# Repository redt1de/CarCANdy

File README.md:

# CarCANdy

# TODO:
- (V2) re-wire the RJ45 connector so pairs or together and in order
- add "live" capture to cli that will read from serial

# SN65HVD233DR Mode select pin (Rs): 
    high speed mode:    JP 2->1 and solder RS
    slope control mode: JP 2->1 and open RS
    low power mode:     JP 2->3

# Aux Ports
    include/AuxPorts.h
    AUX1: digital, UART,PWM
        28: RX,D28
        29: TX,D28

    AUX2: digital,analog,UART,PWM
        24: TX,D24,A10
        25: RX,D25,A11

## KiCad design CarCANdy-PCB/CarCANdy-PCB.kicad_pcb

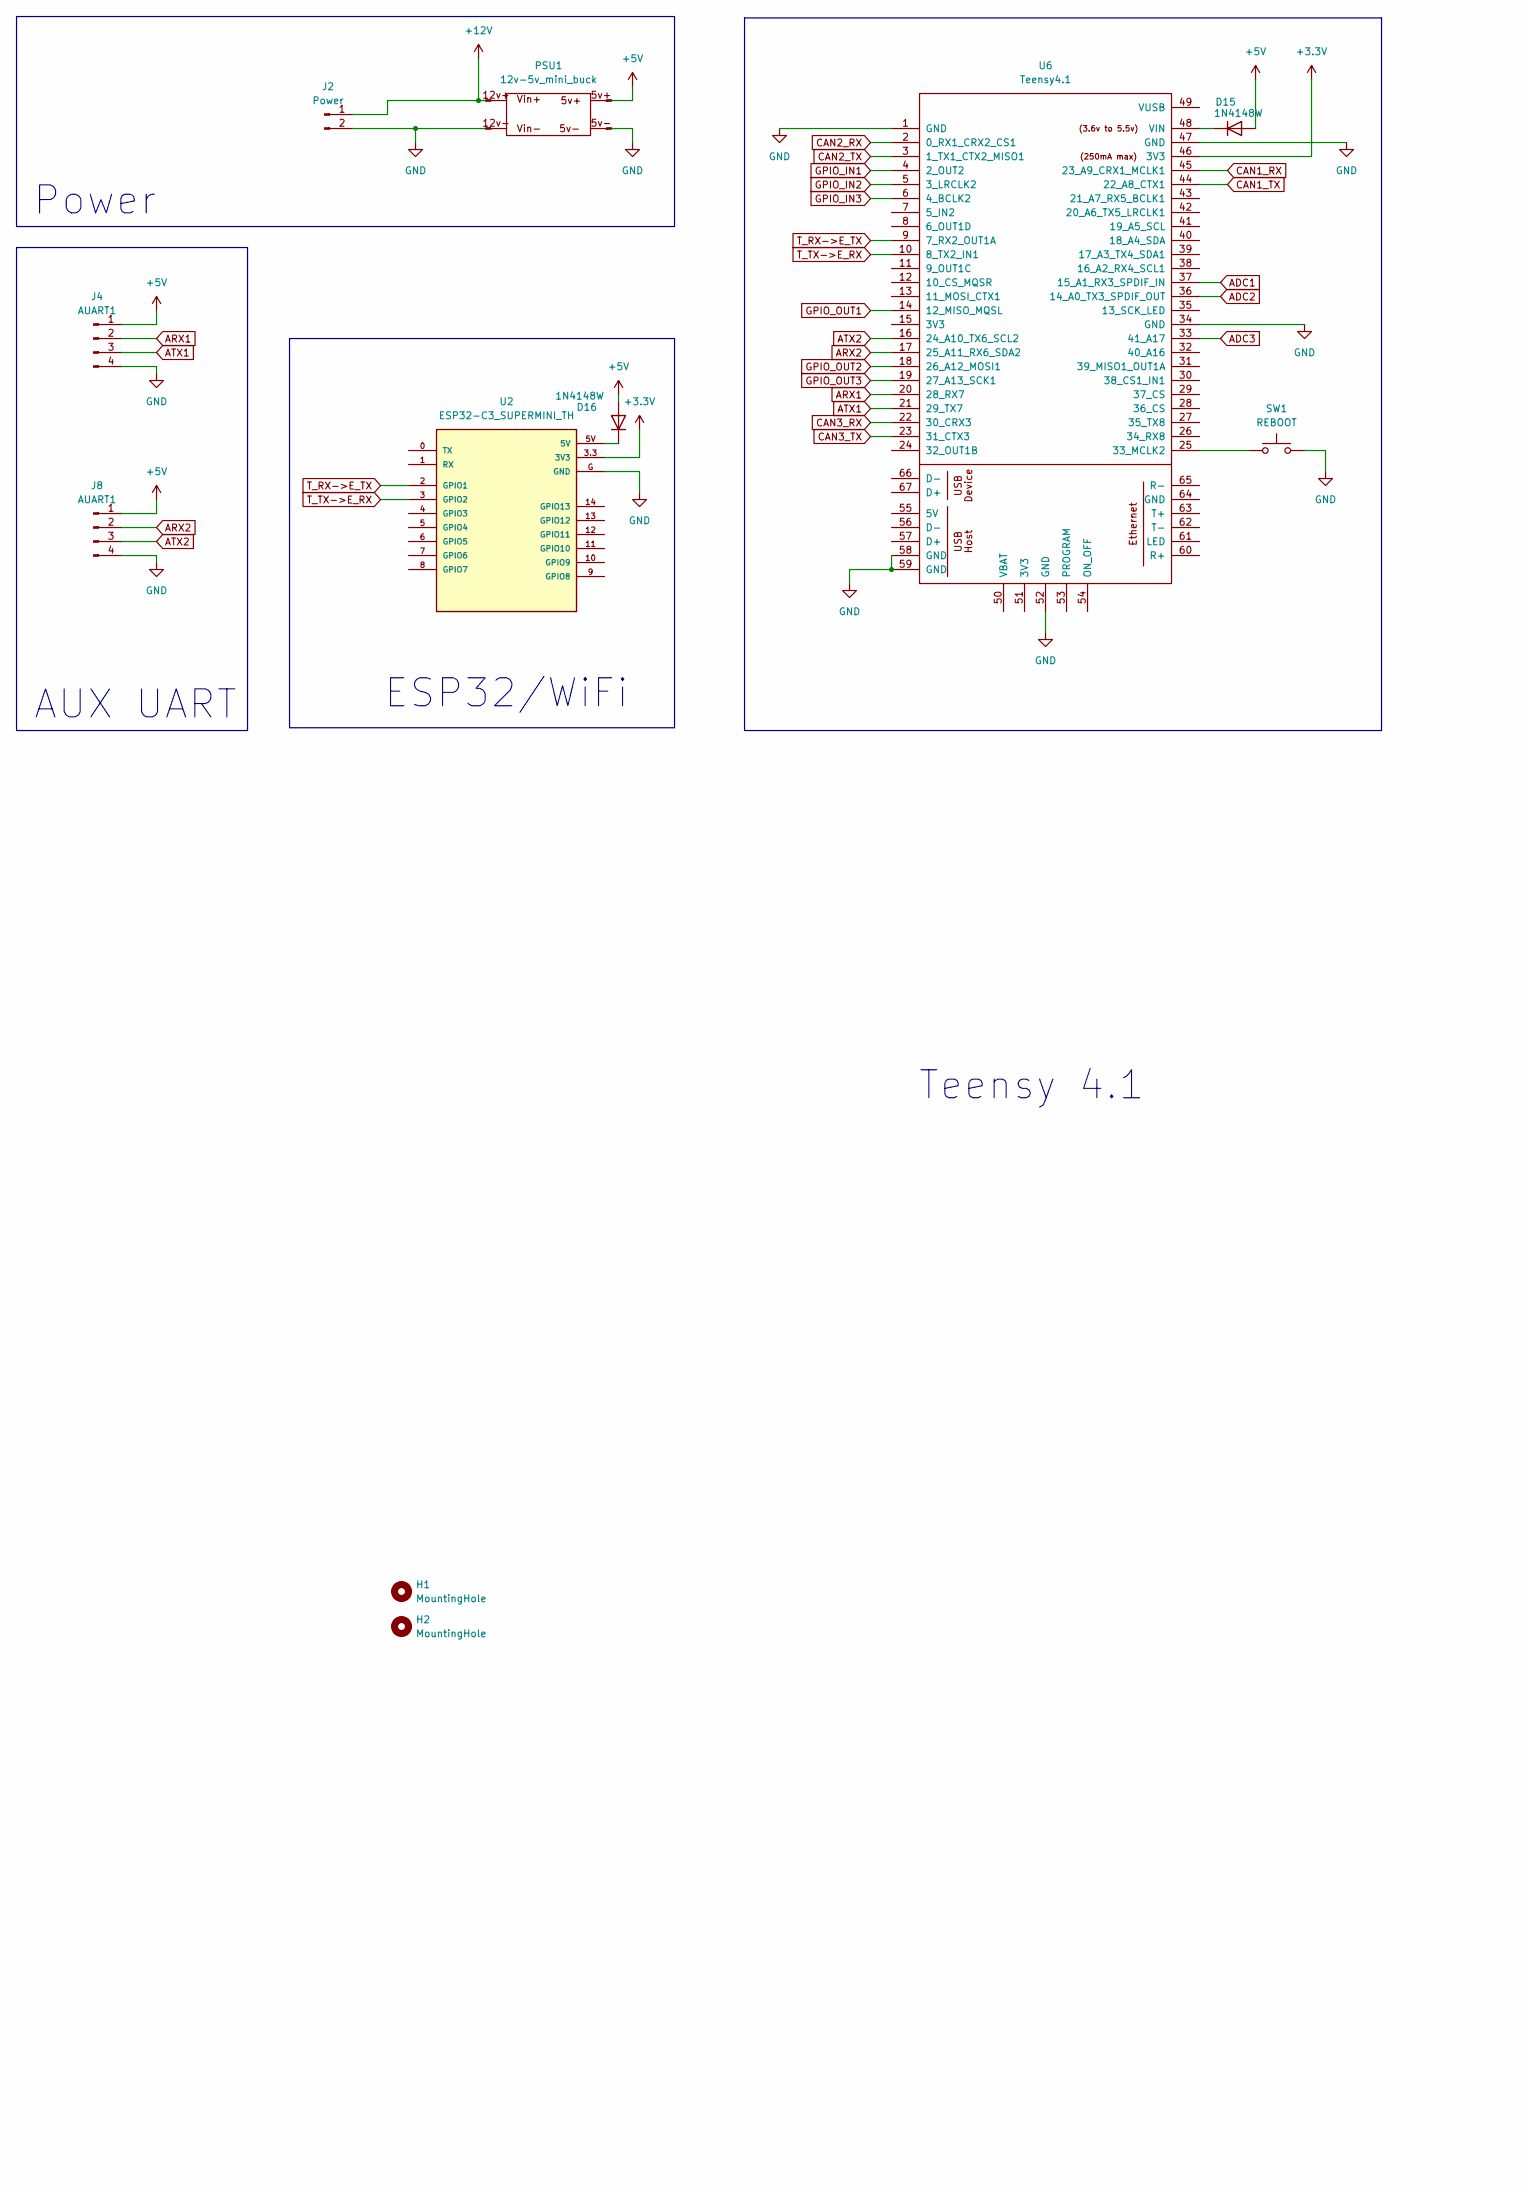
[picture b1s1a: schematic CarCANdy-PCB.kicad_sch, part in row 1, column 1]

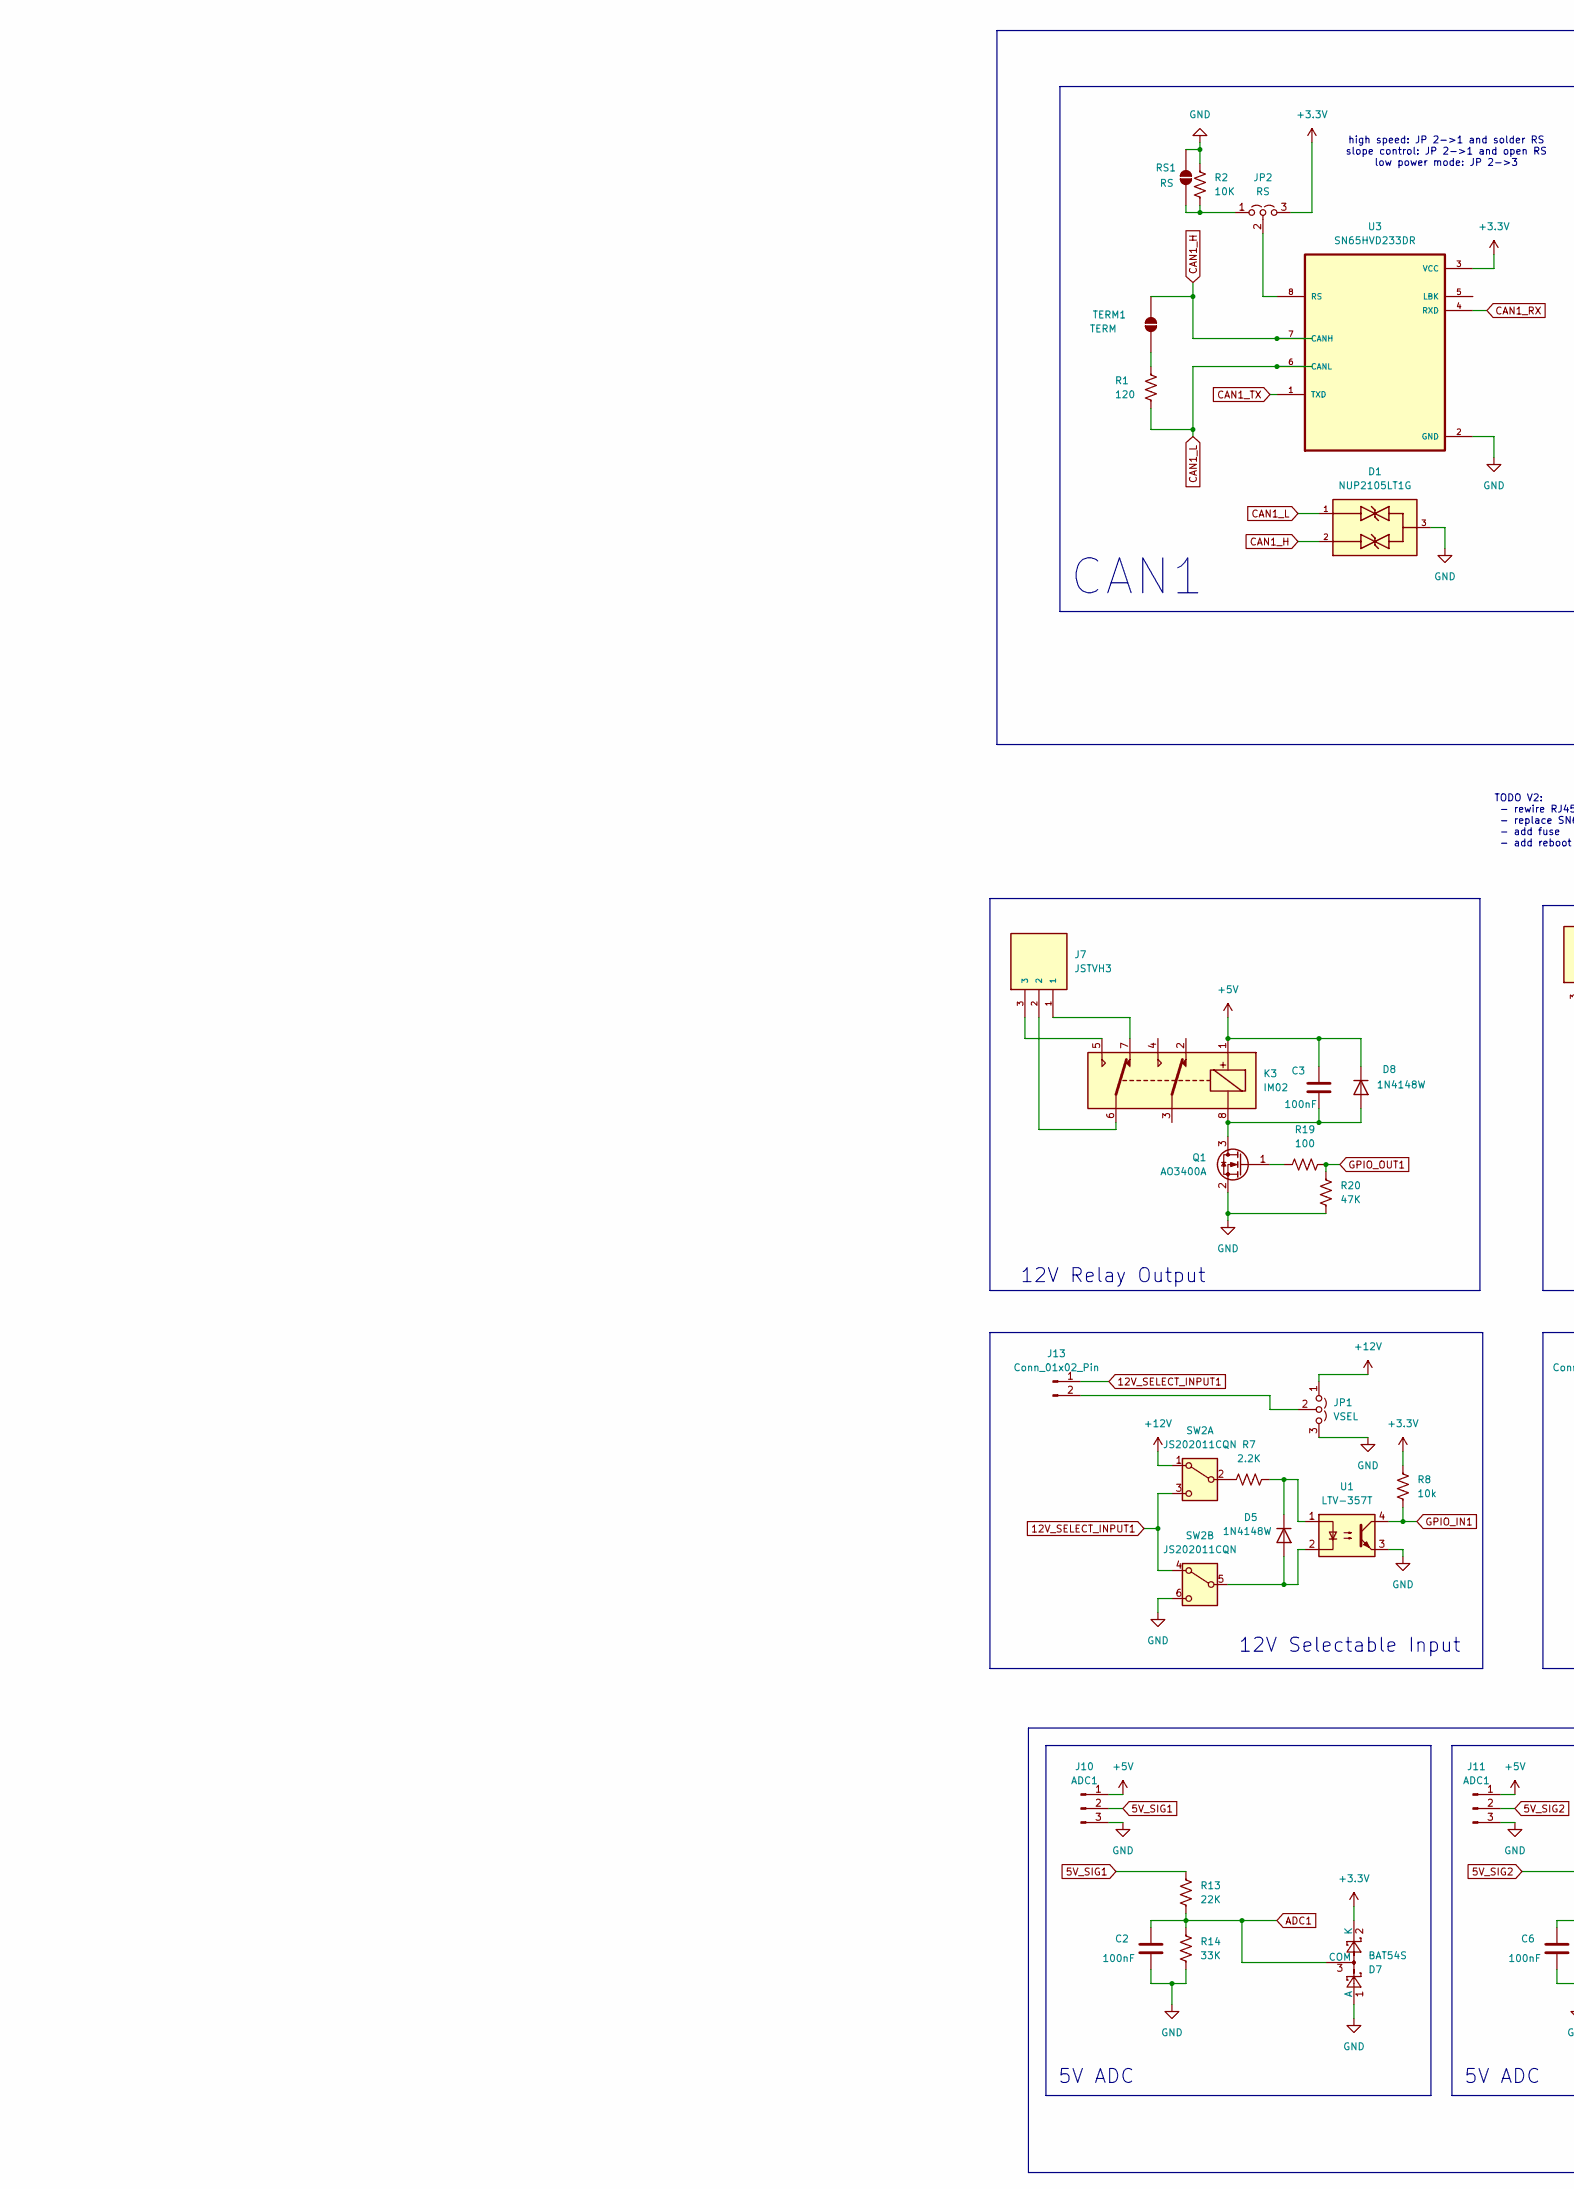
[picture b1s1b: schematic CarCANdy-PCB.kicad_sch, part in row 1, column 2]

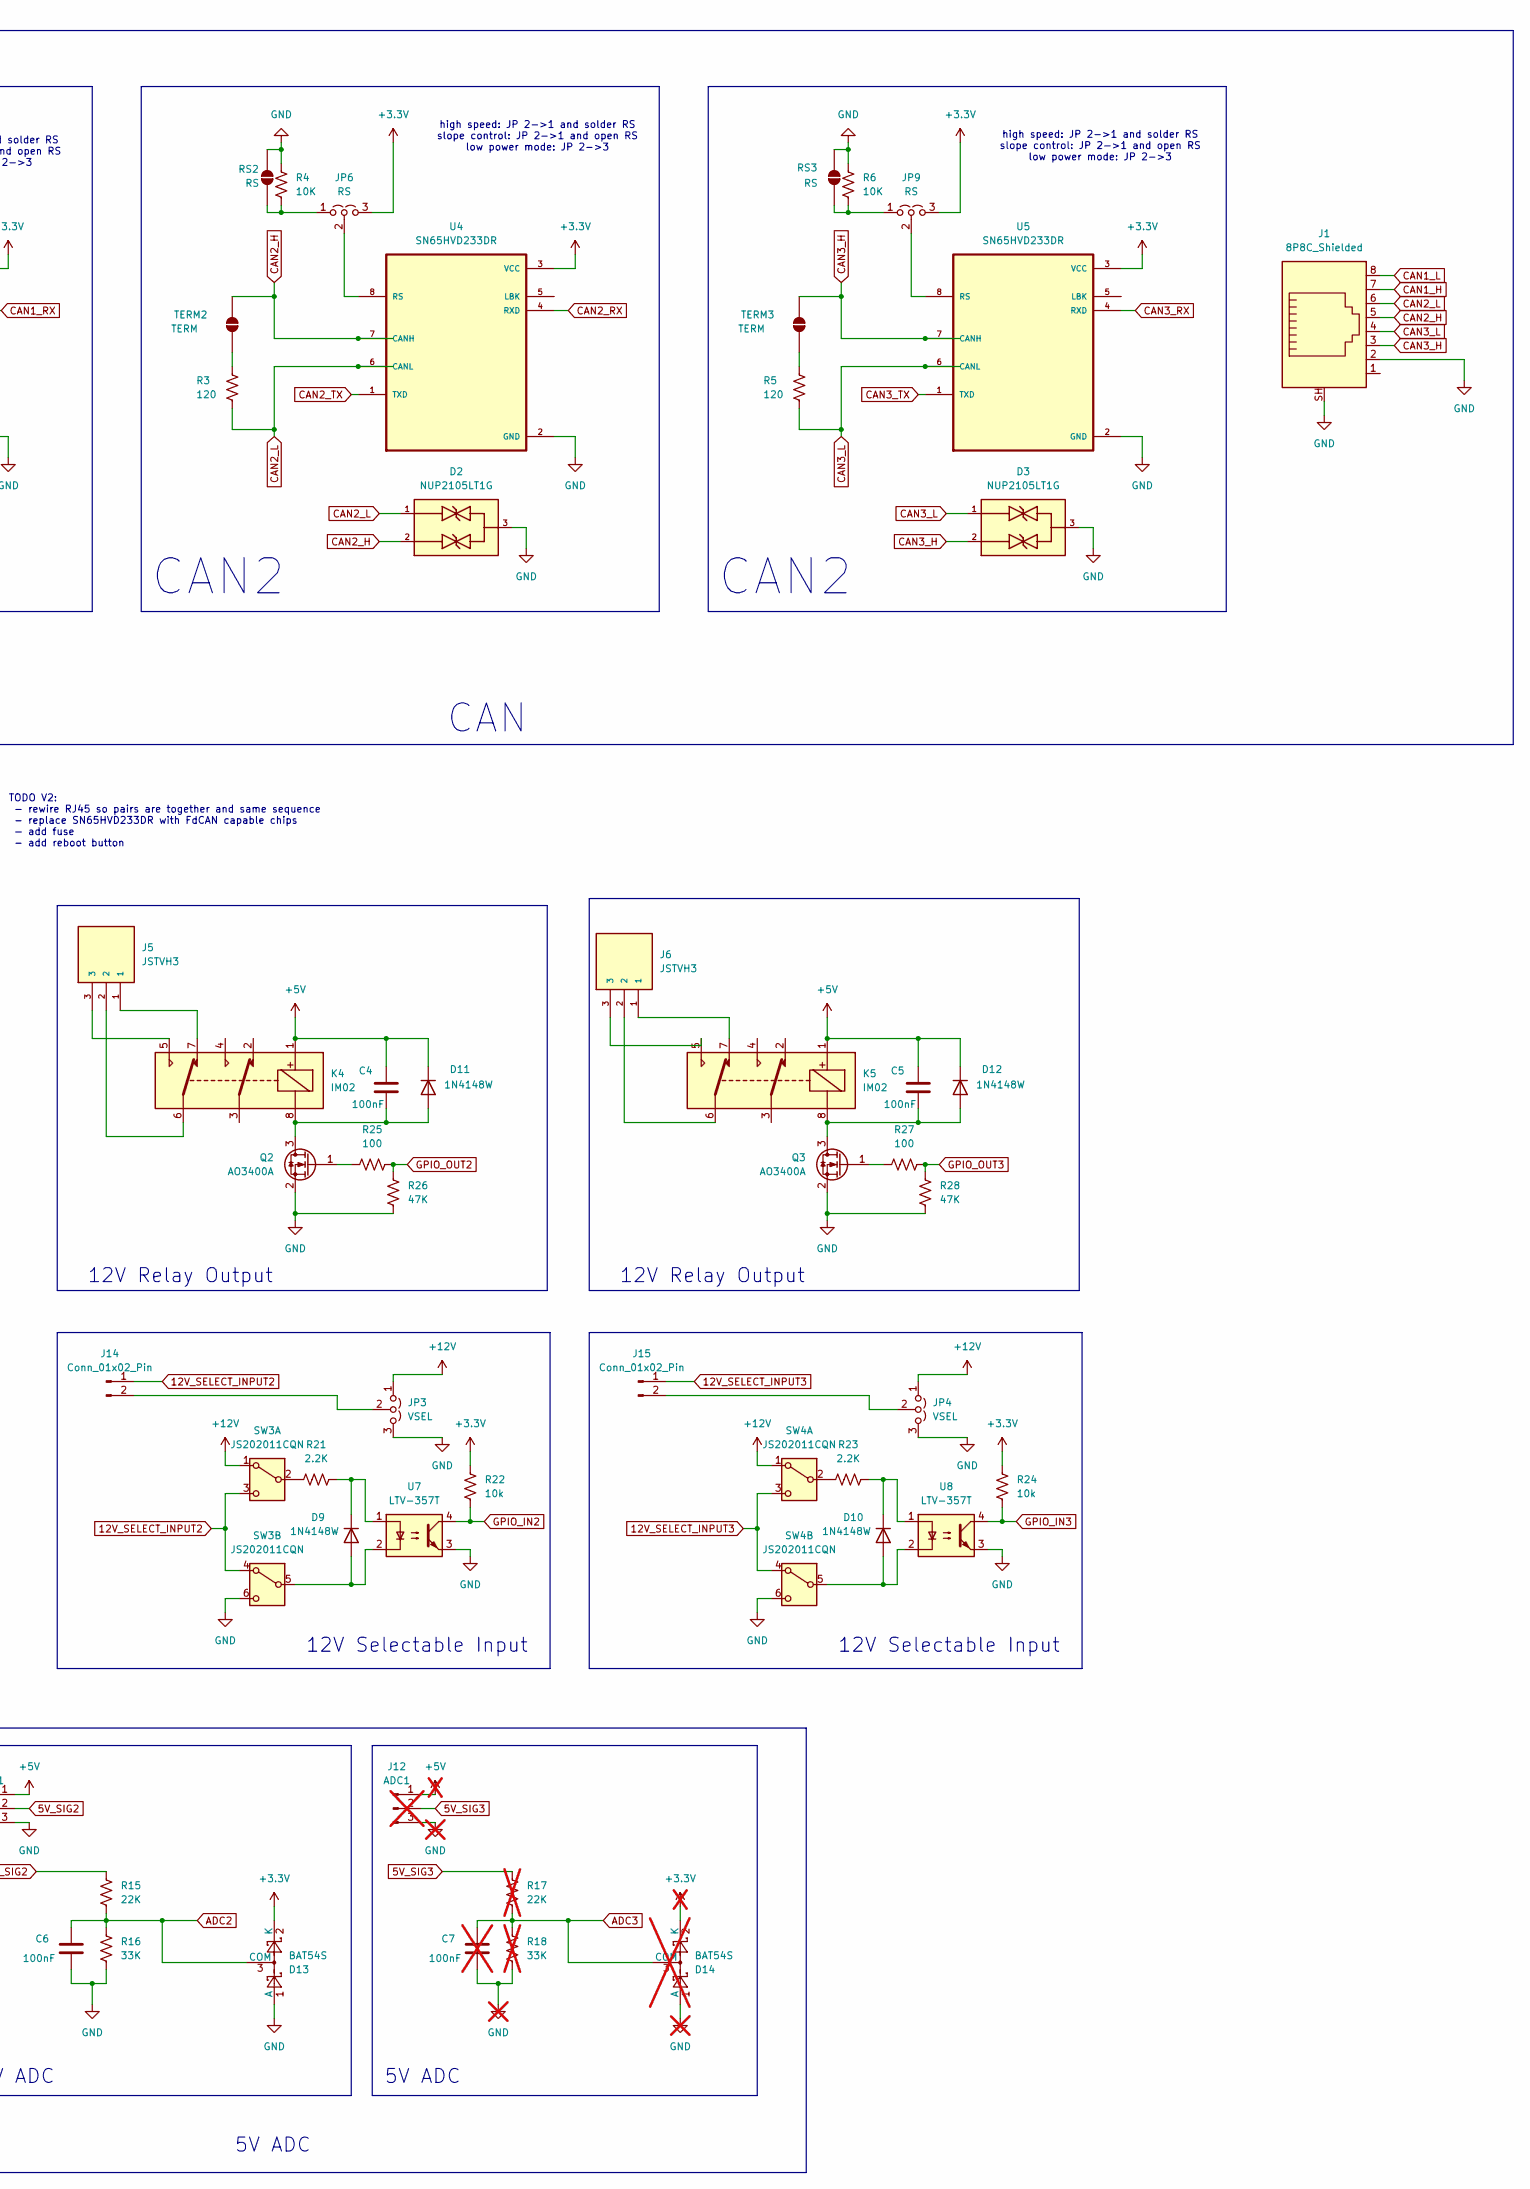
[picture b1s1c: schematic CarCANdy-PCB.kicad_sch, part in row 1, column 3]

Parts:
C2, C3, C4, C5, C6: 100nF; C_1206_3216Metric_Pad1.33x1.80mm_HandSolder
C7: 100nF; C_0603_1608Metric_Pad1.08x0.95mm_HandSolder; not fitted
D1, D2, D3: NUP2105LT1G; SOT-23-3; PARTREV 10
D5, D8, D9, D10, D11, D12, D15, D16: 1N4148W; D_SOD-123
D7, D13: BAT54S; SOT-23
D14: BAT54S; SOT-23; not fitted
H1, H2: MountingHole; MountingHole_3.2mm_M3
J1: 8P8C_Shielded; RJ45_RCH_RC01937
J2: Power; JST_VH_S2P-VH_1x02_P3.96mm_Horizontal
J4, J8: AUART1; JST_XH_S4B-XH-A-1_1x04_P2.50mm_Horizontal
J5, J6, J7: JSTVH3; JST_VH_S3P-VH_1x03_P3.96mm_Horizontal
J10, J11: ADC1; JST_XH_S3B-XH-A-1_1x03_P2.50mm_Horizontal
J12: ADC1; JST_EH_S3B-EH_1x03_P2.50mm_Horizontal; not fitted
J13, J14, J15: Conn_01x02_Pin; JST_XH_S2B-XH-A-1_1x02_P2.50mm_Horizontal
JP1, JP3, JP4: VSEL; PinHeader_1x03_P2.00mm_Vertical
JP2, JP6, JP9: RS; PinHeader_1x03_P2.00mm_Vertical
K3, K4, K5: IM02; RELAY_IM06TS
PSU1: 12v-5v_mini_buck; mini12v-5v_buck
Q1, Q2, Q3: AO3400A; SOT-23
R1, R3, R5: 120; R_1206_3216Metric_Pad1.30x1.75mm_HandSolder
R2, R4, R6: 10K; R_1206_3216Metric_Pad1.30x1.75mm_HandSolder
R7, R21, R23: 2.2K; R_1206_3216Metric_Pad1.30x1.75mm_HandSolder
R8, R22, R24: 10k; R_1206_3216Metric_Pad1.30x1.75mm_HandSolder
R13, R15: 22K; R_1206_3216Metric_Pad1.30x1.75mm_HandSolder
R14, R16: 33K; R_1206_3216Metric_Pad1.30x1.75mm_HandSolder
R17: 22K; R_0603_1608Metric_Pad0.98x0.95mm_HandSolder; not fitted
R18: 33K; R_0603_1608Metric_Pad0.98x0.95mm_HandSolder; not fitted
R19, R25, R27: 100; R_1206_3216Metric_Pad1.30x1.75mm_HandSolder
R20, R26, R28: 47K; R_1206_3216Metric_Pad1.30x1.75mm_HandSolder
RS1, RS2, RS3: RS; SolderJumper-2_P1.3mm_Open_TrianglePad1.0x1.5mm
SW1: REBOOT; SW_Push_1P1T_NO_CK_KMR2
SW2, SW3, SW4: JS202011CQN
TERM1, TERM2, TERM3: TERM; SolderJumper-2_P1.3mm_Open_TrianglePad1.0x1.5mm
U1, U7, U8: LTV-357T; SOP-4_3.8x4.1mm_P2.54mm
U2: ESP32-C3_SUPERMINI_TH; MODULE_ESP32-C3_SUPERMINI_TH
U3, U4, U5: SN65HVD233DR; SOIC127P599X175-8N
U6: Teensy4.1; Teensy41

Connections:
5V_SIG1: J10.2, R13.1
5V_SIG2: J11.2, R15.1
12V_SELECT_INPUT1: J13.1, SW2.3 (C), SW2.4 (A)
12V_SELECT_INPUT2: J14.1, SW3.3 (C), SW3.4 (A)
12V_SELECT_INPUT3: J15.1, SW4.3 (C), SW4.4 (A)
+3.3V: D7.2 (K), D13.2 (K), D14.2 (K), JP2.3 (B), JP6.3 (B), JP9.3 (B), R8.2, R22.2, R24.2, U2.3.3 (3V3), U3.3 (VCC), U4.3 (VCC), U5.3 (VCC), U6.46 (3V3)
+5V: C3.1, C4.1, C5.1, D8.1 (K), D11.1 (K), D12.1 (K), D15.2 (A), D16.2 (A), J4.1, J8.1, J10.1, J11.1, J12.1, K3.1, K4.1, K5.1, PSU1.5v+ (Pin_4)
+12V: J2.1, JP1.1 (A), JP3.1 (A), JP4.1 (A), PSU1.12v+ (Pin_1), SW2.1 (A), SW3.1 (A), SW4.1 (A)
ADC1: C2.1, D7.3 (COM), R13.2, R14.1, U6.37 (15_A1_RX3_SPDIF_IN)
ADC2: C6.1, D13.3 (COM), R15.2, R16.1, U6.36 (14_A0_TX3_SPDIF_OUT)
ADC3: C7.1, D14.3 (COM), R17.2, R18.1, U6.33 (41_A17)
ARX1: J4.2, U6.20 (28_RX7)
ARX2: J8.2, U6.17 (25_A11_RX6_SDA2)
ATX1: J4.3, U6.21 (29_TX7)
ATX2: J8.3, U6.16 (24_A10_TX6_SCL2)
CAN1_H: D1.2, J1.7, TERM1.2 (B), U3.7 (CANH)
CAN1_L: D1.1, J1.8, R1.2, U3.6 (CANL)
CAN1_RX: U3.4 (RXD), U6.45 (23_A9_CRX1_MCLK1)
CAN1_TX: U3.1 (TXD), U6.44 (22_A8_CTX1)
CAN2_H: D2.2, J1.5, TERM2.2 (B), U4.7 (CANH)
CAN2_L: D2.1, J1.6, R3.2, U4.6 (CANL)
CAN2_RX: U4.4 (RXD), U6.2 (0_RX1_CRX2_CS1)
CAN2_TX: U4.1 (TXD), U6.3 (1_TX1_CTX2_MISO1)
CAN3_H: D3.2, J1.3, TERM3.2 (B), U5.7 (CANH)
CAN3_L: D3.1, J1.4, R5.2, U5.6 (CANL)
CAN3_RX: U5.4 (RXD), U6.22 (30_CRX3)
CAN3_TX: U5.1 (TXD), U6.23 (31_CTX3)
GND: C2.2, C6.2, C7.2, D1.3, D2.3, D3.3, D7.1 (A), D13.1 (A), D14.1 (A), J1.2, J1.SH, J2.2, J4.4, J8.4, J10.3, J11.3, J12.3, JP1.3 (B), JP3.3 (B), JP4.3 (B), PSU1.5v- (Pin_3), PSU1.12v- (Pin_2), Q1.2 (S), Q2.2 (S), Q3.2 (S), R2.1, R4.1, R6.1, R14.2, R16.2, R18.2, R20.2, R26.2, R28.2, RS1.2 (B), RS2.2 (B), RS3.2 (B), SW1.2, SW2.6 (C), SW3.6 (C), SW4.6 (C), U1.3, U2.G (GND), U3.2 (GND), U4.2 (GND), U5.2 (GND), U6.1 (GND), U6.34 (GND), U6.47 (GND), U6.52 (GND), U6.58 (GND), U6.59 (GND), U7.3, U8.3
GPIO_IN1: R8.1, U1.4, U6.4 (2_OUT2)
GPIO_IN2: R22.1, U6.5 (3_LRCLK2), U7.4
GPIO_IN3: R24.1, U6.6 (4_BCLK2), U8.4
GPIO_OUT1: R19.1, R20.1, U6.14 (12_MISO_MQSL)
GPIO_OUT2: R25.1, R26.1, U6.18 (26_A12_MOSI1)
GPIO_OUT3: R27.1, R28.1, U6.19 (27_A13_SCK1)
unnamed: D5.2 (A), SW2.5 (B), U1.2
unnamed: D5.1 (K), R7.2, U1.1
unnamed: C3.2, D8.2 (A), K3.8, Q1.3 (D)
unnamed: D9.2 (A), SW3.5 (B), U7.2
unnamed: D9.1 (K), R21.2, U7.1
unnamed: D10.2 (A), SW4.5 (B), U8.2
unnamed: D10.1 (K), R23.2, U8.1
unnamed: C4.2, D11.2 (A), K4.8, Q2.3 (D)
unnamed: C5.2, D12.2 (A), K5.8, Q3.3 (D)
unnamed: D15.1 (K), U6.48 (VIN)
unnamed: D16.1 (K), U2.5V
unnamed: J5.1, K4.7
unnamed: J5.2, K4.6
unnamed: J5.3, K4.5
unnamed: J6.1, K5.7
unnamed: J6.2, K5.6
unnamed: J6.3, K5.5
unnamed: J7.1, K3.7
unnamed: J7.2, K3.6
unnamed: J7.3, K3.5
unnamed: J12.2, R17.1
unnamed: J13.2, JP1.2 (C)
unnamed: J14.2, JP3.2 (C)
unnamed: J15.2, JP4.2 (C)
unnamed: JP2.1 (A), R2.2, RS1.1 (A)
unnamed: JP2.2 (C), U3.8 (RS)
unnamed: JP6.1 (A), R4.2, RS2.1 (A)
unnamed: JP6.2 (C), U4.8 (RS)
unnamed: JP9.1 (A), R6.2, RS3.1 (A)
unnamed: JP9.2 (C), U5.8 (RS)
unnamed: Q1.1 (G), R19.2
unnamed: Q2.1 (G), R25.2
unnamed: Q3.1 (G), R27.2
unnamed: R7.1, SW2.2 (B)
unnamed: R21.1, SW3.2 (B)
unnamed: R23.1, SW4.2 (B)
unnamed: R1.1, TERM1.1 (A)
unnamed: R3.1, TERM2.1 (A)
unnamed: R5.1, TERM3.1 (A)
unnamed: SW1.1, U6.25 (33_MCLK2)
T_RX->E_TX: U2.2 (GPIO1), U6.9 (7_RX2_OUT1A)
T_TX->E_RX: U2.3 (GPIO2), U6.10 (8_TX2_IN1)

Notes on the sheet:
AUX UART
Power
CAN1
TODO V2: - rewire RJ45 so pairs are together and same sequence - replace SN65HVD233DR with FdCAN capable chips - add fuse - add reboot button
CAN
12V Selectable Input
5V ADC
CAN2
12V Relay Output
high speed: JP 2->1 and solder RS slope control: JP 2->1 and open RS low power mode: JP 2->3
ESP32/WiFi
Teensy 4.1

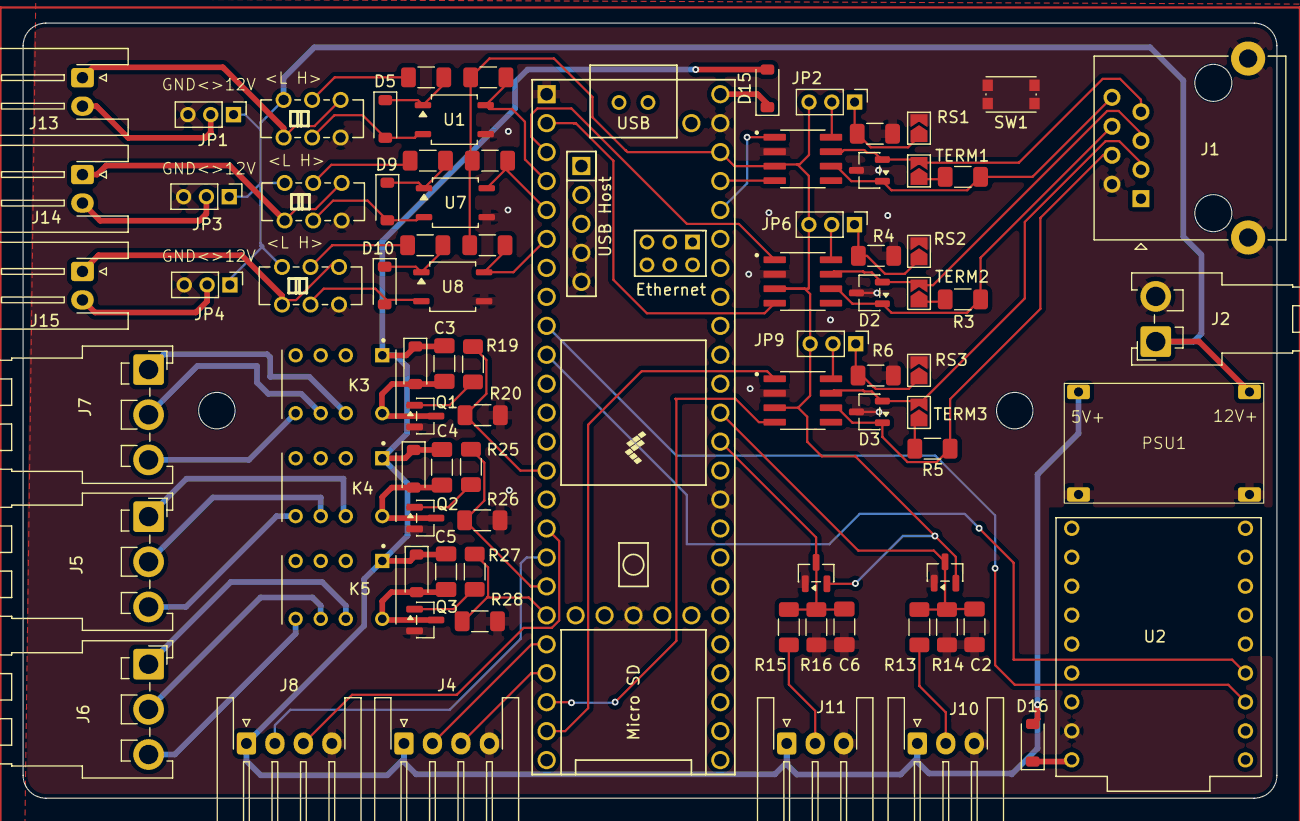
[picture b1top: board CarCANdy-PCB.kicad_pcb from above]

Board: 2 copper layers, 110.0 x 68.0 mm, 85 parts (0 on the bottom side), 74 nets.

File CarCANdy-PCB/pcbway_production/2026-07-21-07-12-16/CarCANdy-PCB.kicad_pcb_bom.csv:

Designator,Quantity,Value,Footprint,Package,MPN,DNP,Mount_Type,Description,KiLib_Generator,MF,MAXIMUM_PACKAGE_HEIGHT,Price,Check_prices,STANDARD,PARTREV,SnapEDA_Link,MP,MANUFACTURER,Availability,SNAPEDA_PN,Sim.Device,Sim.Pins,CREATOR
"C2, C3, C4, C5, C6, C7",6,100nF,C_0603_1608Metric_Pad1.08x0.95mm_HandSolder,,,,smt,Unpolarized capacitor,SMD_2terminal_chip_molded,,,,,,,,,,,,,,
"D1, D2, D3",3,NUP2105LT1G,SOT95P237X111-3N,SOT-23-3 ON Semiconductor,,,smt,Dual Bi-Directional TVS Diode 350W 3-Pin SOT-23 | ON Semiconductor NUP2105LT1G,,ON Semiconductor,1.11mm,None,https://www.snapeda.com/parts/NUP2105LT1G/Onsemi/view-part/?ref=eda,IPC-7351B,10,https://www.snapeda.com/parts/NUP2105LT1G/Onsemi/view-part/?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,NUP2105LT1G,Onsemi,In Stock,NUP2105LT1G,,,
"D10, D11, D12, D5, D8, D9",6,1N4148W,D_SOD-123,,,,smt,"75V 0.15A Fast Switching Diode, SOD-123",,,,,,,,,,,,,D,1=K 2=A,
"D13, D14, D7",3,BAT54S,SOT-23,,,,smt,"Vr 30V, If 200mA, Dual schottky barrier diode, in series, SOT-323",package/gullwing,,,,,,,,,,,,,,
J1,1,8P8C_Shielded,RJ45_RCH_RC01937,,,,tht,"RJ connector, 8P8C (8 positions 8 connected), RJ31/RJ32/RJ33/RJ34/RJ35/RJ41/RJ45/RJ49/RJ61, Shielded",,,,,,,,,,,,,,,
"J2, J2, J2, J2",4,Power,JST_EH_S2B-EH_1x02_P2.50mm_Horizontal,,,,tht,"Generic connector, single row, 01x02, script generated",connector/JST,,,,,,,,,,,,,,
"J3, J5, J6, J7, J9",5,TB004-508-03BE,CUI_TB004-508-03BE,None,,,tht,"2~24 Poles, Screw Type, Horizontal, 5.08 Pitch, 24~12 (AWG), Terminal Block Connector",,Same Sky,,None,https://www.snapeda.com/parts/TB004-508-03BE/Same+Sky/view-p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,Manufacturer Recommendations,,https://www.snapeda.com/parts/TB004-508-03BE/Same+Sky/view-p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,TB004-508-03BE,CUI,In Stock,,,,
"J4, J8",2,AUART1,JST_PH_S4B-PH-K_1x04_P2.00mm_Horizontal,,,,tht,"Generic connector, single row, 01x04, script generated",connector/JST,,,,,,,,,,,,,,
"K3, K4, K5",3,IM02,RELAY_IM06TS,,,,tht,"IM Relay, standard version, monostable, switching current 2/5A, power 60W/62.5VA, voltage 220VDC/250VAC",,,,,,,,,,,,,,,
PSU1,1,12v-5v_mini_buck,mini12v-5v_buck,,,,smt,"Generic connector, single row, 01x04, script generated",,,,,,,,,,,,,,,
"Q1, Q2, Q3",3,AO3400A,SOT-23,,,,smt,"30V Vds, 5.7A Id, N-Channel MOSFET, SOT-23",package/gullwing,,,,,,,,,,,,,,
"R1, R3, R5",3,120,R_0603_1608Metric_Pad0.98x0.95mm_HandSolder,,,,smt,"Resistor, US symbol",SMD_2terminal_chip_molded,,,,,,,,,,,,,,
"R13, R15, R17",3,22K,R_0603_1608Metric_Pad0.98x0.95mm_HandSolder,,,,smt,"Resistor, US symbol",SMD_2terminal_chip_molded,,,,,,,,,,,,,,
"R14, R16, R18",3,33K,R_0603_1608Metric_Pad0.98x0.95mm_HandSolder,,,,smt,"Resistor, US symbol",SMD_2terminal_chip_molded,,,,,,,,,,,,,,
"R19, R25, R27",3,100,R_0603_1608Metric_Pad0.98x0.95mm_HandSolder,,,,smt,"Resistor, US symbol",SMD_2terminal_chip_molded,,,,,,,,,,,,,,
"R2, R4, R6",3,10K,R_0603_1608Metric_Pad0.98x0.95mm_HandSolder,,,,smt,"Resistor, US symbol",SMD_2terminal_chip_molded,,,,,,,,,,,,,,
"R20, R26, R28",3,47K,R_0603_1608Metric_Pad0.98x0.95mm_HandSolder,,,,smt,"Resistor, US symbol",SMD_2terminal_chip_molded,,,,,,,,,,,,,,
"R21, R23, R7",3,2.2K,R_0603_1608Metric_Pad0.98x0.95mm_HandSolder,,,,smt,"Resistor, US symbol",SMD_2terminal_chip_molded,,,,,,,,,,,,,,
"R22, R24, R8",3,10k,R_0603_1608Metric_Pad0.98x0.95mm_HandSolder,,,,smt,"Resistor, US symbol",SMD_2terminal_chip_molded,,,,,,,,,,,,,,
"SW2, SW3, SW4",3,JS202011CQN,JS202011CQN,,,,tht,"Switch, dual pole double throw, separate symbols",,,,,,,,,,,,,,,
"U1, U7, U8",3,LTV-357T,SO-4_4.4x3.6mm_P2.54mm,,,,smt,"DC Optocoupler, Vce 35V, CTR 50%, SO-4",,,,,,,,,,,,,,,
U2,1,ESP32-C3_SUPERMINI_TH,MODULE_ESP32-C3_SUPERMINI_TH,Package,,,tht,Super tiny ESP32-C3 board,,Espressif Systems,,None,https://www.snapeda.com/parts/ESP32-C3%20SuperMini_TH/Espres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,IPC-7351B,,https://www.snapeda.com/parts/ESP32-C3%20SuperMini_TH/Espres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,ESP32-C3 SuperMini_TH,Espressif Systems,Not in stock,,,,DIZAR
"U3, U4, U5",3,SN65HVD233DR,SOIC127P599X175-8N,SOIC-8 Texas Instruments,,,smt,"3.3 V CAN Transceiver with Standby Mode, Loopback",,Texas Instruments,,None,https://www.snapeda.com/parts/SN65HVD233DR/Texas+Instruments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,,,https://www.snapeda.com/parts/SN65HVD233DR/Texas+Instruments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,SN65HVD233DR,,In Stock,,,,
U6,1,Teensy4.1,Teensy41,,,,tht,,,,,,,,,,,,,,,,
